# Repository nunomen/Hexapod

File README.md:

# Hexa

This project started as an idea to build a reliable low cost hexapod robot and at the same time improving the existing designs, distinguishing it from the others by having a symmetrical form factor.

To know more about the project check the wiki pages of the repository.

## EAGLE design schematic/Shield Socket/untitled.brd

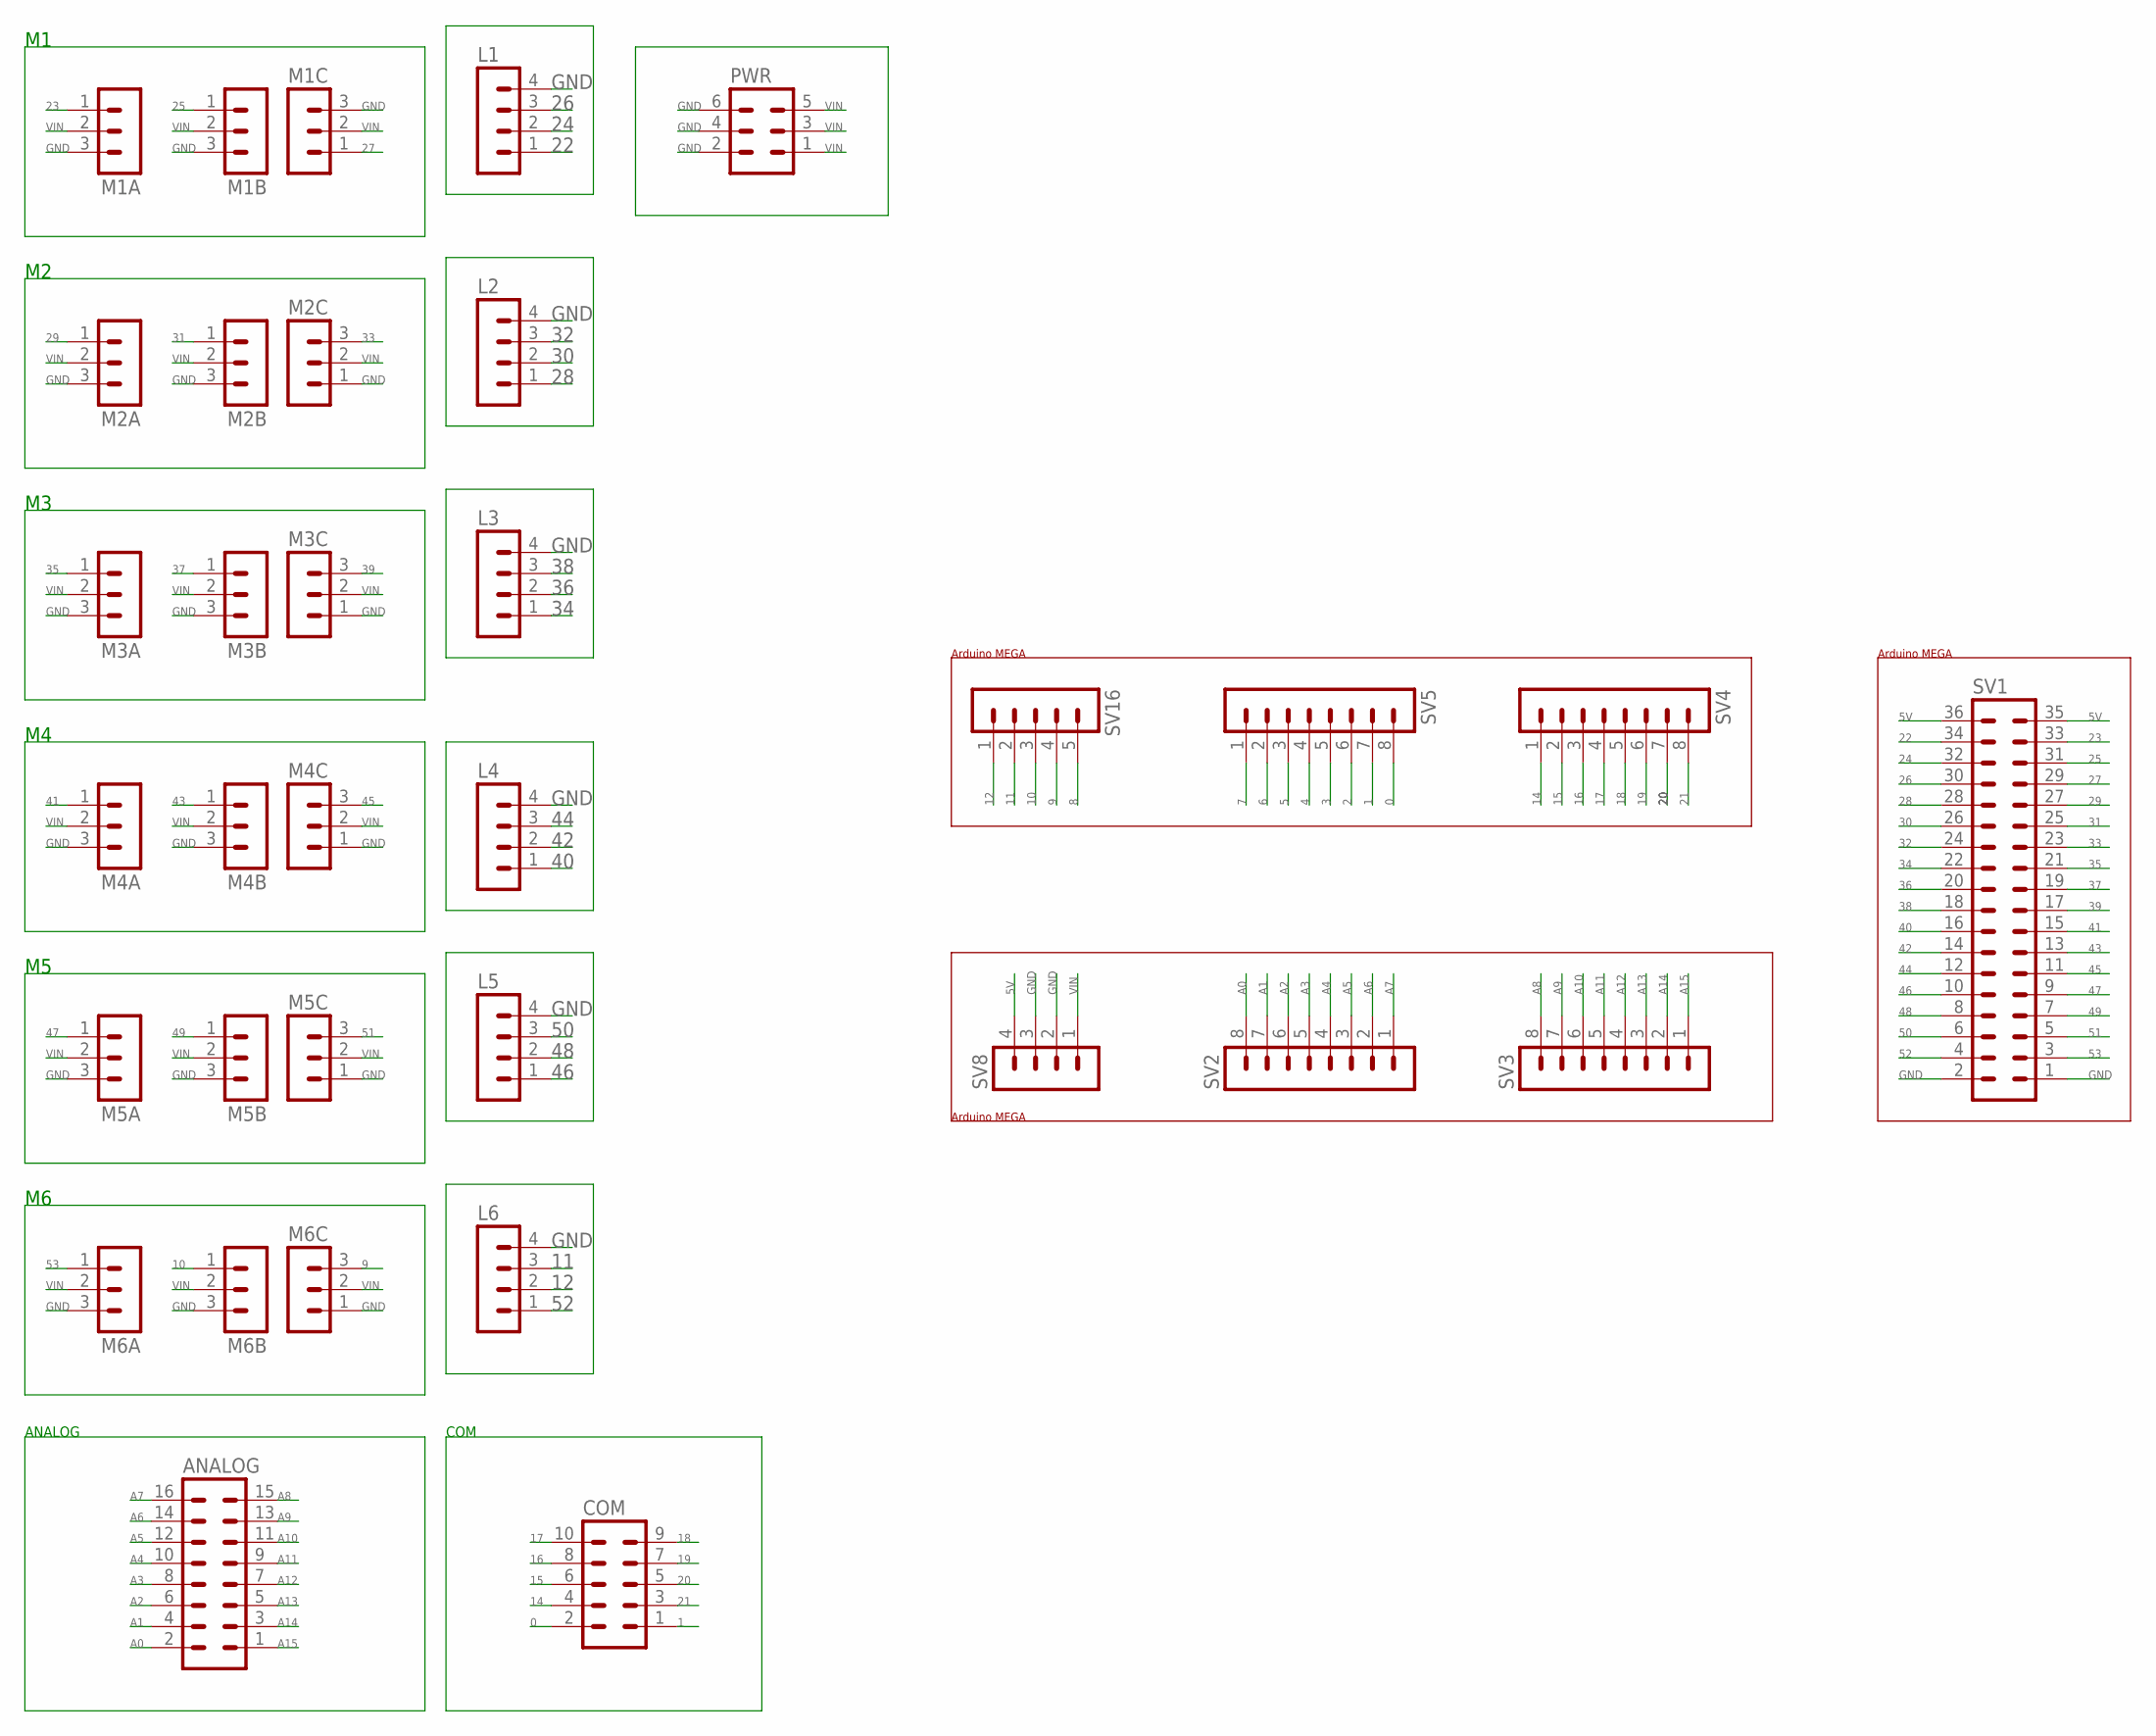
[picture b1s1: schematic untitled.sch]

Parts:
ANALOG: MA08-2
COM: MA05-2
L1, L2, L3, L4, L5, L6: MA04-1
M1A, M1B, M1C, M2A, M2B, M2C, M3A, M3B, M3C, M4A, M4B, M4C, M5A, M5B, M5C, M6A, M6B, M6C: MA03-1
PWR: MA03-2
SV1: MA18-2
SV2, SV3, SV4, SV5: MA08-1
SV8: MA04-1
SV16: MA05-1

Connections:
0: COM.2, SV5.8
1: COM.1, SV5.7
2: SV5.6
3: SV5.5
4: SV5.4
5: SV5.3
5V: SV1.35, SV1.36, SV8.4
6: SV5.2
7: SV5.1
8: SV16.5
9: M6C.3, SV16.4
10: M6B.1, SV16.3
11: L6.3, SV16.2
12: L6.2, SV16.1
14: COM.4, SV4.1
15: COM.6, SV4.2
16: COM.8, SV4.3
17: COM.10, SV4.4
18: COM.9, SV4.5
19: COM.7, SV4.6
20: COM.5, SV4.7
21: COM.3, SV4.8
22: L1.1, SV1.34
23: M1A.1, SV1.33
24: L1.2, SV1.32
25: M1B.1, SV1.31
26: L1.3, SV1.30
27: M1C.1, SV1.29
28: L2.1, SV1.28
29: M2A.1, SV1.27
30: L2.2, SV1.26
31: M2B.1, SV1.25
32: L2.3, SV1.24
33: M2C.3, SV1.23
34: L3.1, SV1.22
35: M3A.1, SV1.21
36: L3.2, SV1.20
37: M3B.1, SV1.19
38: L3.3, SV1.18
39: M3C.3, SV1.17
40: L4.1, SV1.16
41: M4A.1, SV1.15
42: L4.2, SV1.14
43: M4B.1, SV1.13
44: L4.3, SV1.12
45: M4C.3, SV1.11
46: L5.1, SV1.10
47: M5A.1, SV1.9
48: L5.2, SV1.8
49: M5B.1, SV1.7
50: L5.3, SV1.6
51: M5C.3, SV1.5
52: L6.1, SV1.4
53: M6A.1, SV1.3
A0: ANALOG.2, SV2.8
A1: ANALOG.4, SV2.7
A2: ANALOG.6, SV2.6
A3: ANALOG.8, SV2.5
A4: ANALOG.10, SV2.4
A5: ANALOG.12, SV2.3
A6: ANALOG.14, SV2.2
A7: ANALOG.16, SV2.1
A8: ANALOG.15, SV3.8
A9: ANALOG.13, SV3.7
A10: ANALOG.11, SV3.6
A11: ANALOG.9, SV3.5
A12: ANALOG.7, SV3.4
A13: ANALOG.5, SV3.3
A14: ANALOG.3, SV3.2
A15: ANALOG.1, SV3.1
GND: L1.4, L2.4, L3.4, L4.4, L5.4, L6.4, M1A.3, M1B.3, M1C.3, M2A.3, M2B.3, M2C.1, M3A.3, M3B.3, M3C.1, M4A.3, M4B.3, M4C.1, M5A.3, M5B.3, M5C.1, M6A.3, M6B.3, M6C.1, PWR.2, PWR.4, PWR.6, SV1.1, SV1.2, SV8.2, SV8.3
VIN: M1A.2, M1B.2, M1C.2, M2A.2, M2B.2, M2C.2, M3A.2, M3B.2, M3C.2, M4A.2, M4B.2, M4C.2, M5A.2, M5B.2, M5C.2, M6A.2, M6B.2, M6C.2, PWR.1, PWR.3, PWR.5, SV8.1

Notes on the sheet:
Arduino MEGA
ANALOG
COM

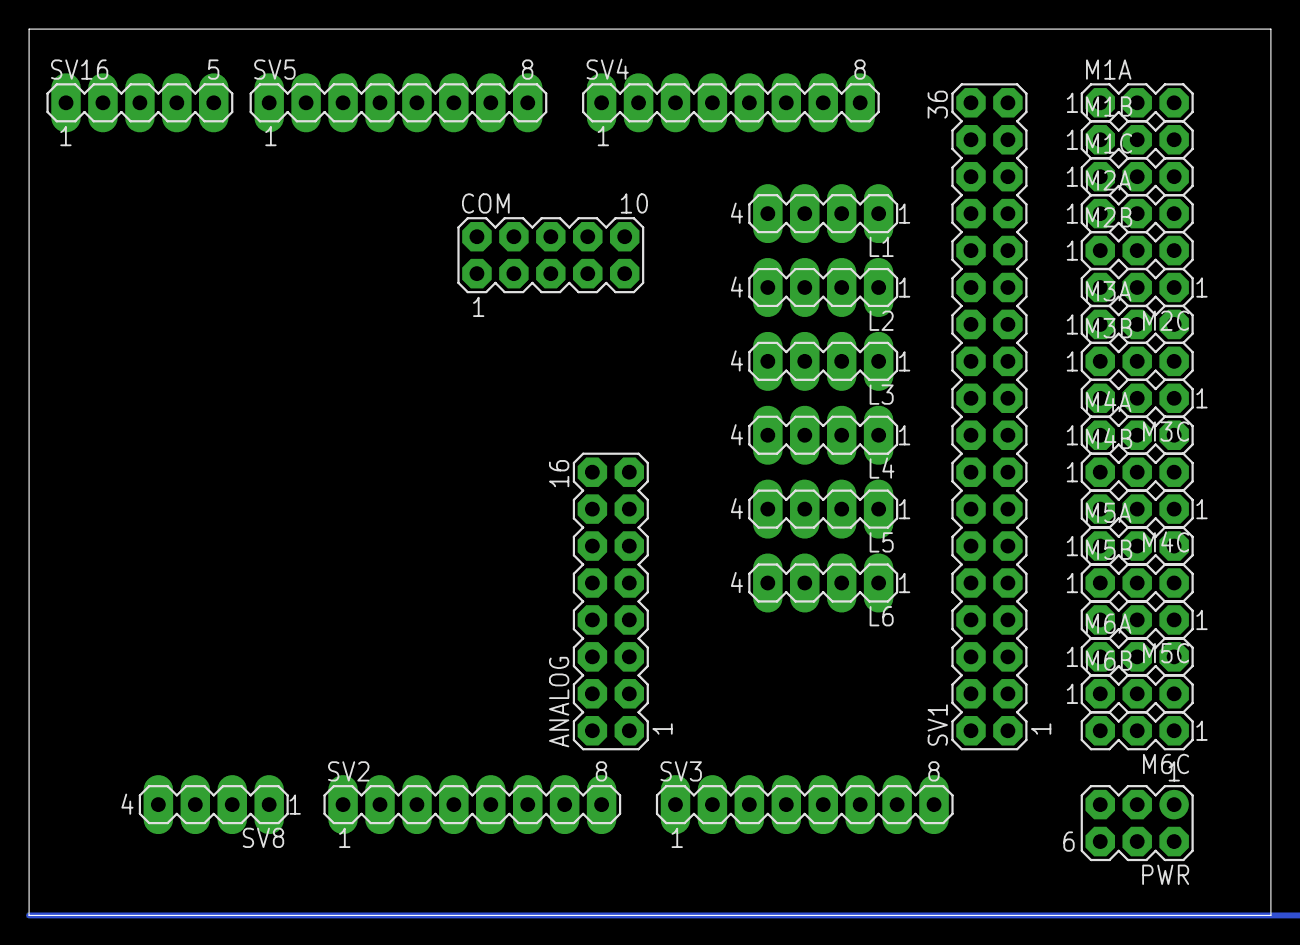
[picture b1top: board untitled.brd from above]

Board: 2 copper layers, 85.4 x 61.0 mm, 34 parts (0 on the bottom side), 65 nets.

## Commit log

2015-06-07 3D model of hexapod
2015-06-09 Added model, code relative to the joints
2015-06-09 File extension updated
    from .txt to .h
2015-06-14 Added eagle files
2015-07-14 Packet class
2015-07-14 Organizing source files
2015-07-15 primeira versão do protocolo
2015-07-15 Class Packet
    Actualizar classe packet
2015-07-16 First Communication with Python
2015-07-16 Cenas do Charuto
2015-07-17 Atributos de um objecto done
2015-07-17 Dicionario adicionado
2015-07-17 Flag do pacote
2015-07-18 Reorganizacão dos ficheiros
2015-07-18 Packet class completed
2015-07-20 Remove Line initiators and terminator
2015-07-20 Serial Packet Communication
2015-07-22 Added Leg,Robot and modified packet cpp
2015-07-22 isto
2015-07-22 Revert "isto"
    This reverts commit 6084668321a1ca13d145da3801d31a2bdfb6b399.
2015-07-22 Deleted termination characters and modified initiation characters to reduce redundancy
2015-07-22 Dont know
2015-07-28 Adicionado o state
2015-07-28 Teste
2015-07-29 Transformation Matrices
    First Version
2015-07-30 Alteracao do state para uma versao estavel que consegue descodificar o pacote
2015-07-30 Limpeza da pasta
2015-07-30 testeCat
    bla
2015-07-30 Revert "testeCat"
    This reverts commit f6620a3bc6c745aa207415d1c9e69cbcf72ad33c.
2015-07-30 Actualizacao do protocolo_serial
2015-08-02 Deleting old files
2015-08-02 Class changes for State, Robot& State + Exemplo Led's
2015-08-03 Versao estavel. Interligacao entre todas as classes.
2015-09-14 Paste organized
2015-09-21 Nova versão
    Matriz DH corrigida. Novos referenciais DH para considerar o centro do
    hexapod, respeitam a orientação oposta dos servos depois da alteração
    das patas (alteração ao arm). Aplicável a todas as patas.
2015-09-21 Variables Renaming
2015-09-24 Jorge Martins's 1st version
    Adopting Jorge Martins' code. First version of the adaptation
2015-09-25 Minor changes, no bug correction
    Adventures and bug correction attempts, reorganized the code
    aesthetically
2015-09-28 Irrelevant
    displayleg commentary
    organization in files
2015-09-28 Direct Kinematics Working
    Fixed errors in the DH table and in the transformation matrices
2015-09-28 Minor format change
    Very tiny table alignment
2015-09-29 Inverse kinematics progress
    It's working we think, for one leg <3
2015-09-29 Deleted junk files
    from matlab
2015-09-29 Direct kinematics done
    Needs to be tested
2015-09-29 Legs display function
    just the name
2015-09-29 Minor changes
    Started developping new vw, need more geometric info
2016-01-29 Added useful information
2016-01-30 - Revisions for python3
2016-01-31 Links about similar hexapod robot projects
2016-02-01 Objective: test all pins associated with servos
2016-02-02 First working script - 1 leg tested
2016-02-03 LegTester: sets the specified leg to home position LegTester_Walker: simple walking cycle with 1 leg for demo
2016-02-04 Sketch of the communication procedure.
2016-02-05 Further work onto PacketHandler
2016-02-09 Refactoring code for python 3
2016-02-09 More refactoring.
2016-02-09 Main program structure added.
2016-02-10 Added comments to better explain the behaviour of the methods of PacketHandler class.
2016-02-10 Removing old files and added queue and vector template implementations.
2016-02-11 Debugging reference stuff.
2016-02-11 Implementation of leg class.
2016-02-12 No more errors on compilation.
2016-02-12 Simplification of message to print.
2016-02-12 Debugging stuff.
2016-02-12 changes to the communication
2016-02-13 Running Serial packets.
2016-02-13 Modifications from Nuno
2016-02-13 Modifications by Nuno vol.2
2016-02-13 Header bytes bug solved.
2016-02-13 Serial communication and leg simulation working
2016-02-13 Debugging messages done.
2016-02-13 More debugging information added.
2016-02-14 - Debugging messages; - Joint limits defined; - Simulation of legs bug solved. - Some unused code removed.
2016-02-14 Upper case letters improved.
2016-02-23 Code refactoring on the reset command.
2016-02-23 Changed license to GNU v3
2016-02-25 Vasco version
2016-02-25 The shoulder pins no longer are shared with the foot pins... Copypasta is the root of all evils.
2016-02-26 Calibration modifications
2016-02-27 Improved main function of hexapod.
2016-02-27 Now with home and storage positions
2016-02-28 Added image of the shield to put on the wiki.
2016-02-28 Code reorganization
2016-03-01 Improvement of shield image
2016-03-03 Walking procedure test
2016-03-03 Bugs on forward motion solved
2016-04-10 Some refactoring in the code.
2016-04-23 Now have preprocessor file for constants of the robot.
2016-04-23 Arduino main function refactored.
2016-10-16 Refactoring the main python code
2016-10-16 Refactored robot classes
2016-10-16 Robot State Refactored
